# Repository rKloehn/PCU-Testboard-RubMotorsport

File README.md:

# PCU-Testboard-RubMotorsport

## Overview
The Powertrain Control Board test board (PCU test board for short) was developed in 2020 for the Drivetrain assembly in order to test the functions for the pneumatic switching and coupling of the RUB20 in advance. For this reason, the board contains all the necessary peripherals and connections required for the switching and coupling of the RUB20. The board is supplied with a 12V power supply (like the real PCU in the vehicle). On the board there are connections for two 24V solenoid valves and one proportional valve. Furthermore two sensors with 5V supply voltage each can be connected and the current value of the proportional valve can be read out. For testing the functionality of the switching and coupling process, three push buttons and an adjustment potentiometer are available. All mentioned components were fixed on the board. The control and regulation tasks are performed by a STM32F405RG. The microcontroller can be programmed via the SWD interface on the board. 

### Sensors
The drivetrain assembly has two sensors specified, which are required for a displacement control of the clutch. A Hall displacement transducer and a pressure sensor are used. The Hall displacement sensor is from the Novotechnik and is sponsored. The sensor is the TFD-4000 series (data sheet TDF-4000). The exact designation of the ordered sensor is: TFD-4021-624-211-401. This sensor has a measuring range of 24mm and a supply voltage of 5V (4.5...5V). The output signal is in the range of 0.25...4.75V and behaves ratiometrically to Ub. The characteristic curve is rising and the sensor is single-channel. Further characteristics can be taken from the data sheet. It is purchased from the company ADZ Nagano. The pressure sensor has a measurable pressure range of FILL IN DATA HERE and requires a supply voltage of 5V. The output signal, similar to the displacement sensor, is ratiometric and is in the range 0.5...4.5V. The sensor has three conductors and a rising characteristic. Further data can be taken from the data sheet (data sheet ADZ-SME).

### Actuators
The actuator system to be controlled by the test board consists of two 24V solenoid valves and one proportional valve. The 24V solenoid valves are from the company FESTO and have the following type description: VUVG-L10-P53E-T-M5_1P3. These are 5/3 [exhausted] valves with a switch-on time of 10ms, a switch-off time of 30ms and a switch-over time of 16ms. The coil is operated with 24V DC with 1W. Further values can be taken from the data sheet (data sheet solenoid valve). The proportional valve is also from the company FESTO and has the type description: VEAA-L-3-D11-Q4-A4-1-R1. The flow valve is controlled by setting the current from 4-20mA. The operating voltage is 24V DC and the electrical connection is a 4-pin M8 connector. Further data can be found in the data sheet.

### User interface
The aim of the test board is to check whether the intended path control and control of the circuit/clutch works. In order for this to happen early in the development process, the board must function completely independently of other boards (e.g. power supply board) or the steering wheel. Thus, it is necessary that the user has a possibility to simulate the actuation of the clutch or the start of a shifting process. For this reason, there are three push buttons on the board, two buttons for upshifting and downshifting and one button for venting the system at the push of a button. A rotary potentiometer also allows the on/off coupling of the motor gearbox. For programming, as mentioned above, the SWD interface is available to the user. The push buttons are all debounced with a corresponding circuit on the board. 

### Power supply
Several circuits are required for the power supply of the board. In total, exactly three voltage levels are available on the entire PCU test board. The input voltage of the board is 12V DC, which can be provided by a battery or power supply unit. The required current ranges from 0.1A to 0.3A, depending on which peripherals are used. The first voltage level of 5V is achieved by a UA78M05CDCY stepdown converter. The 5V voltage is then either used by the sensors or forms the input voltage for the 5V-3.3V voltage converter. Here a LM2937IMP is used. The 3.3V voltage circuit provides the supply voltage for the microcontroller. The 24V voltage circuit is realized by a StepUp circuit with the MC33063ADG. The 24V are used for the two valves.

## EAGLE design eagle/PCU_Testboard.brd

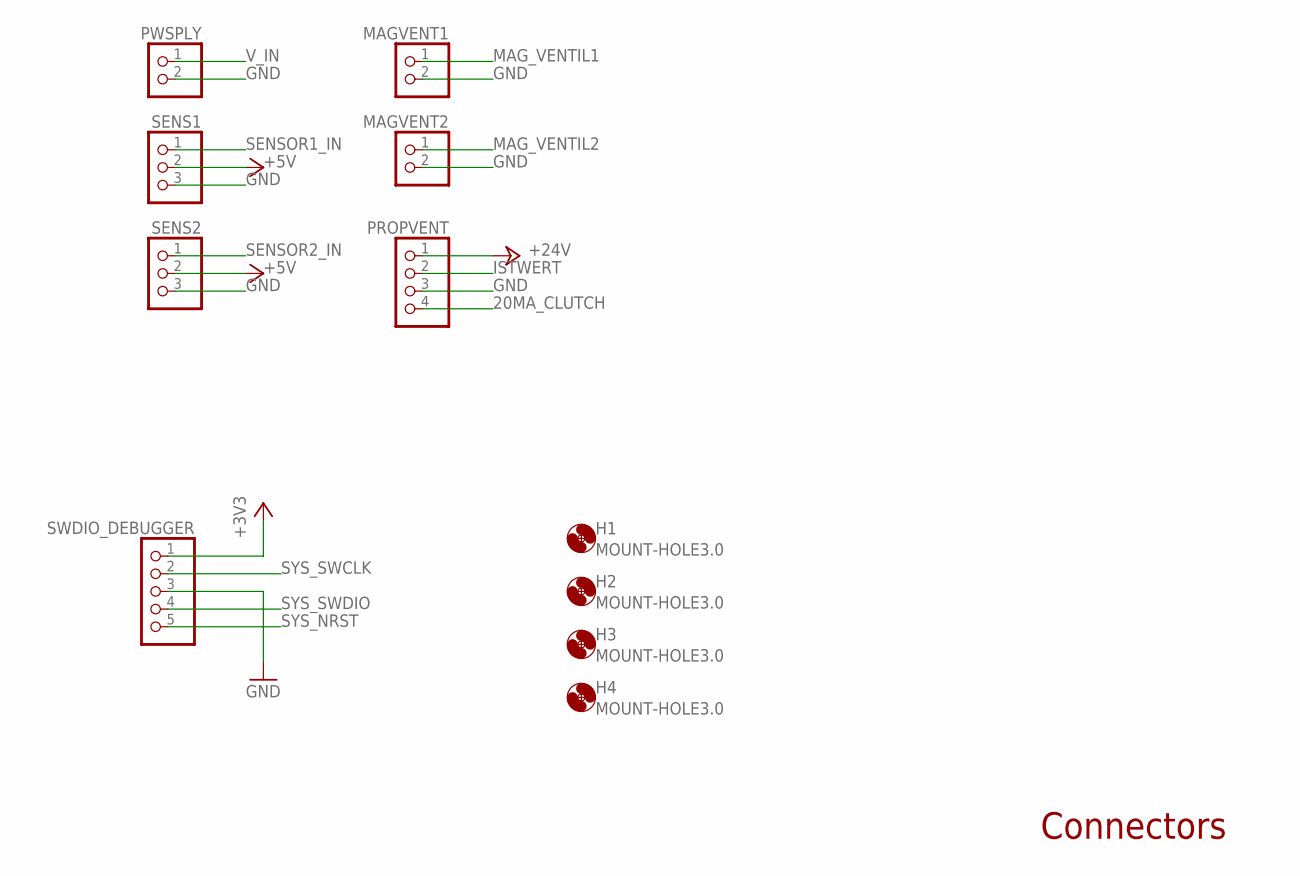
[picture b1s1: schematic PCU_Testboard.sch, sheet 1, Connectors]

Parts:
H1, H2, H3, H4: MOUNT-HOLE3.0; 3,0
MAGVENT1, MAGVENT2: PINHD-1X2; 1X02
PROPVENT: PINHD-1X4; 1X04
PWSPLY: PINHD-1X2; 1X02
SENS1, SENS2: PINHD-1X3; 1X03
SWDIO_DEBUGGER: PINHD-1X5; 1X05

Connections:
20MA_CLUTCH: PROPVENT.4; also elsewhere on the board
+3V3: SWDIO_DEBUGGER.1; also elsewhere on the board
+5V: SENS1.2, SENS2.2; also elsewhere on the board
+24V: PROPVENT.1; also elsewhere on the board
GND: MAGVENT1.2, MAGVENT2.2, PROPVENT.3, PWSPLY.2, SENS1.3, SENS2.3, SWDIO_DEBUGGER.3; also elsewhere on the board
ISTWERT: PROPVENT.2; also elsewhere on the board
MAG_VENTIL1: MAGVENT1.1; also elsewhere on the board
MAG_VENTIL2: MAGVENT2.1; also elsewhere on the board
SENSOR1_IN: SENS1.1; also elsewhere on the board
SENSOR2_IN: SENS2.1; also elsewhere on the board
SYS_NRST: SWDIO_DEBUGGER.5
SYS_SWCLK: SWDIO_DEBUGGER.2; also elsewhere on the board
SYS_SWDIO: SWDIO_DEBUGGER.4; also elsewhere on the board
V_IN: PWSPLY.1; also elsewhere on the board

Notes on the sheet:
Connectors

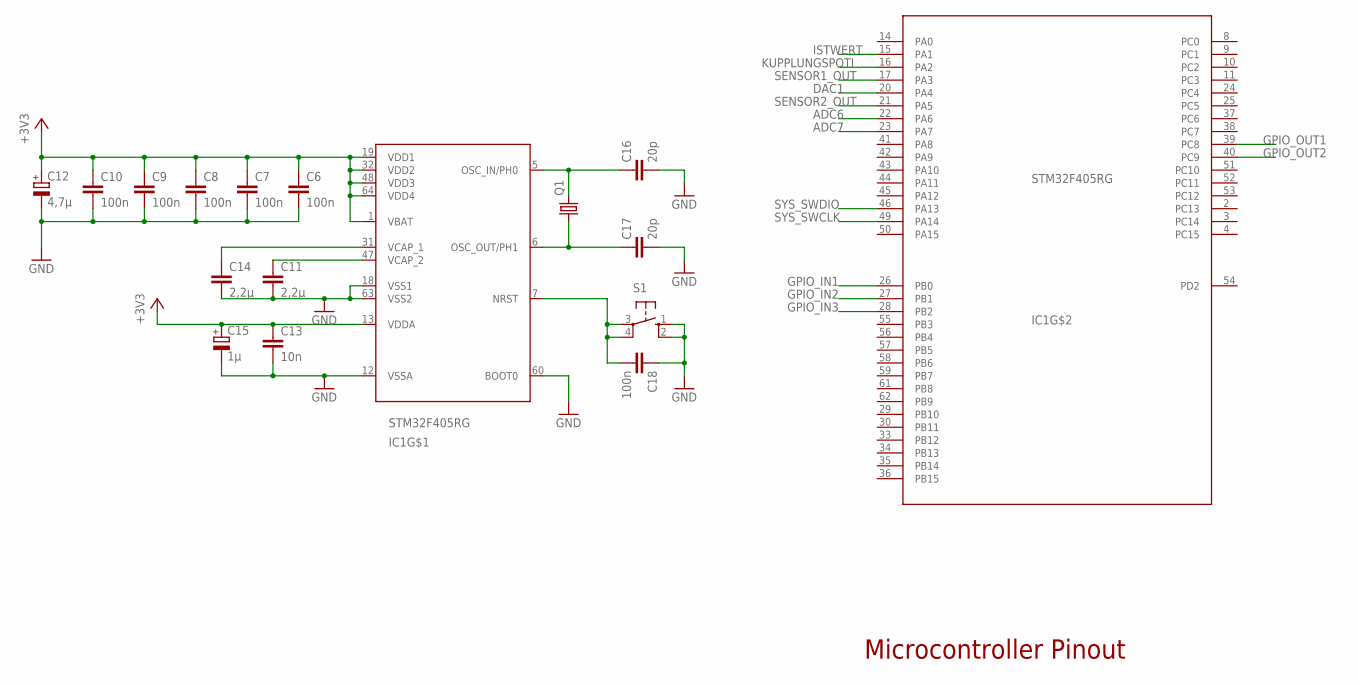
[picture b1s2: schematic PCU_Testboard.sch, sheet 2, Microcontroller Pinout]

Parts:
C6, C7, C8, C9, C10, C18: 100n; C0603
C11, C14: 2,2µ; C0603
C12: 4,7µ; 153CLV-0505
C13: 10n; C0603
C15: 1µ; 153CLV-0505
C16, C17: 20p; C0603
IC1: STM32F405RG; LQFP64
Q1: CRYSTALHC49UP; HC49UP
S1: 10-XX; B3F-10XX

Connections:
+3V3: C6.1, C7.1, C8.1, C9.1, C10.1, C12.+, C13.1, C15.+, IC1.1 (VBAT), IC1.13 (VDDA), IC1.19 (VDD1), IC1.32 (VDD2), IC1.48 (VDD3), IC1.64 (VDD4); also elsewhere on the board
ADC6: IC1.22 (PA6)
ADC7: IC1.23 (PA7)
DAC1: IC1.20 (PA4); also elsewhere on the board
GND: C6.2, C7.2, C8.2, C9.2, C10.2, C11.2, C12.-, C13.2, C14.2, C15.-, C16.2, C17.2, C18.1, IC1.12 (VSSA), IC1.18 (VSS1), IC1.60 (BOOT0), IC1.63 (VSS2), S1.1 (S), S1.2 (S1); also elsewhere on the board
GPIO_IN1: IC1.26 (PB0); also elsewhere on the board
GPIO_IN2: IC1.27 (PB1); also elsewhere on the board
GPIO_IN3: IC1.28 (PB2); also elsewhere on the board
GPIO_OUT1: IC1.39 (PC8); also elsewhere on the board
GPIO_OUT2: IC1.40 (PC9); also elsewhere on the board
ISTWERT: IC1.15 (PA1); also elsewhere on the board
KUPPLUNGSPOTI: IC1.16 (PA2); also elsewhere on the board
unnamed: C14.1, IC1.31 (VCAP_1)
unnamed: C11.1, IC1.47 (VCAP_2)
unnamed: C16.1, IC1.5 (OSC_IN/PH0), Q1.2
unnamed: C17.1, IC1.6 (OSC_OUT/PH1), Q1.1
unnamed: C18.2, IC1.7 (NRST), S1.3, S1.4 (P1)
SENSOR1_OUT: IC1.17 (PA3); also elsewhere on the board
SENSOR2_OUT: IC1.21 (PA5); also elsewhere on the board
SYS_SWCLK: IC1.49 (PA14); also elsewhere on the board
SYS_SWDIO: IC1.46 (PA13); also elsewhere on the board

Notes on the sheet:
Microcontroller Pinout

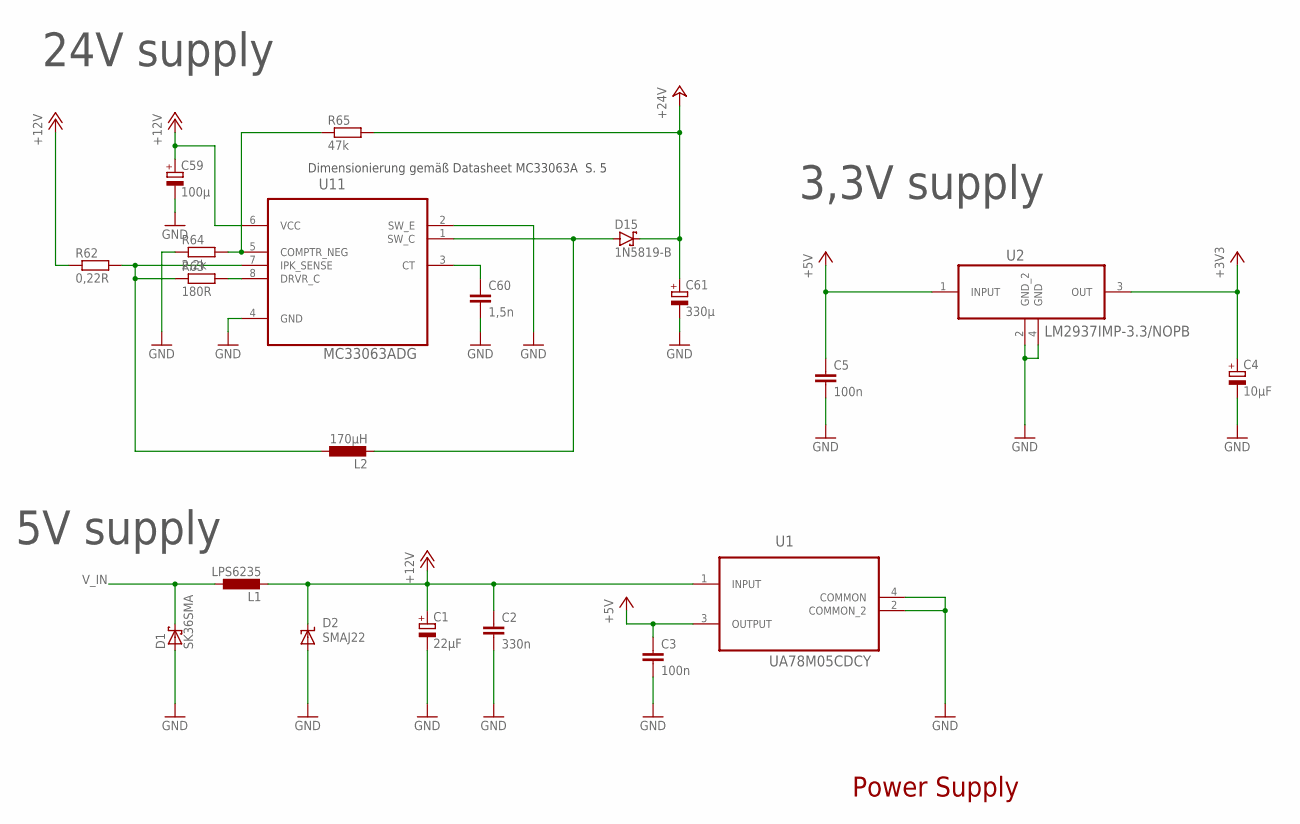
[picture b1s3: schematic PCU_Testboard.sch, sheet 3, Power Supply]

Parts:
C1: 22µF; 153CLV-0605
C2: 330n; C0603
C3, C5: 100n; C0603
C4: 10µF; 153CLV-0807
C59: 100µ; 150CLZ-0810
C60: 1,5n; C0603
C61: 330µ; 153CLV-1010
D1: SK36SMA; DO214AC
D2: SMAJ22; SMA-DO214AC
D15: 1N5819-B; DO41-7.6
L1: LPS6235
L2: 170µH; LPS6235
R62: 0,22R; R0603
R63: 180R; R0603
R64: 2,2k; R0603
R65: 47k; R0603
U1: UA78M05CDCY; SOT230P700X180-4N
U2: LM2937IMP-3.3/NOPB; SOT230P700X180-4N
U11: MC33063ADG; SOIC127P600X175-8N

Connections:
+3V3: C4.+, U2.3 (OUT); also elsewhere on the board
+5V: C3.1, C5.1, U1.3 (OUTPUT), U2.1 (INPUT); also elsewhere on the board
+12V: C1.+, C2.1, C59.+, D2.K (C), L1.2, R62.1, U1.1 (INPUT), U11.6 (VCC); also elsewhere on the board
+24V: C61.+, D15.C, R65.2; also elsewhere on the board
GND: C1.-, C2.2, C3.2, C4.-, C5.2, C59.-, C60.2, C61.-, D1.A, D2.A, R64.1, U1.2 (COMMON_2), U1.4 (COMMON), U2.2 (GND_2), U2.4 (GND), U11.2 (SW_E), U11.4 (GND); also elsewhere on the board
unnamed: C60.1, U11.3 (CT)
unnamed: L2.1, R62.2, R63.1, U11.7 (IPK_SENSE)
unnamed: R63.2, U11.8 (DRVR_C)
unnamed: D15.A, L2.2, U11.1 (SW_C)
unnamed: R64.2, R65.1, U11.5 (COMPTR_NEG)
V_IN: D1.C, L1.1; also elsewhere on the board

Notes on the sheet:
Dimensionierung gemäß Datasheet MC33063A S. 5
24V supply
3,3V supply
5V supply
Power Supply

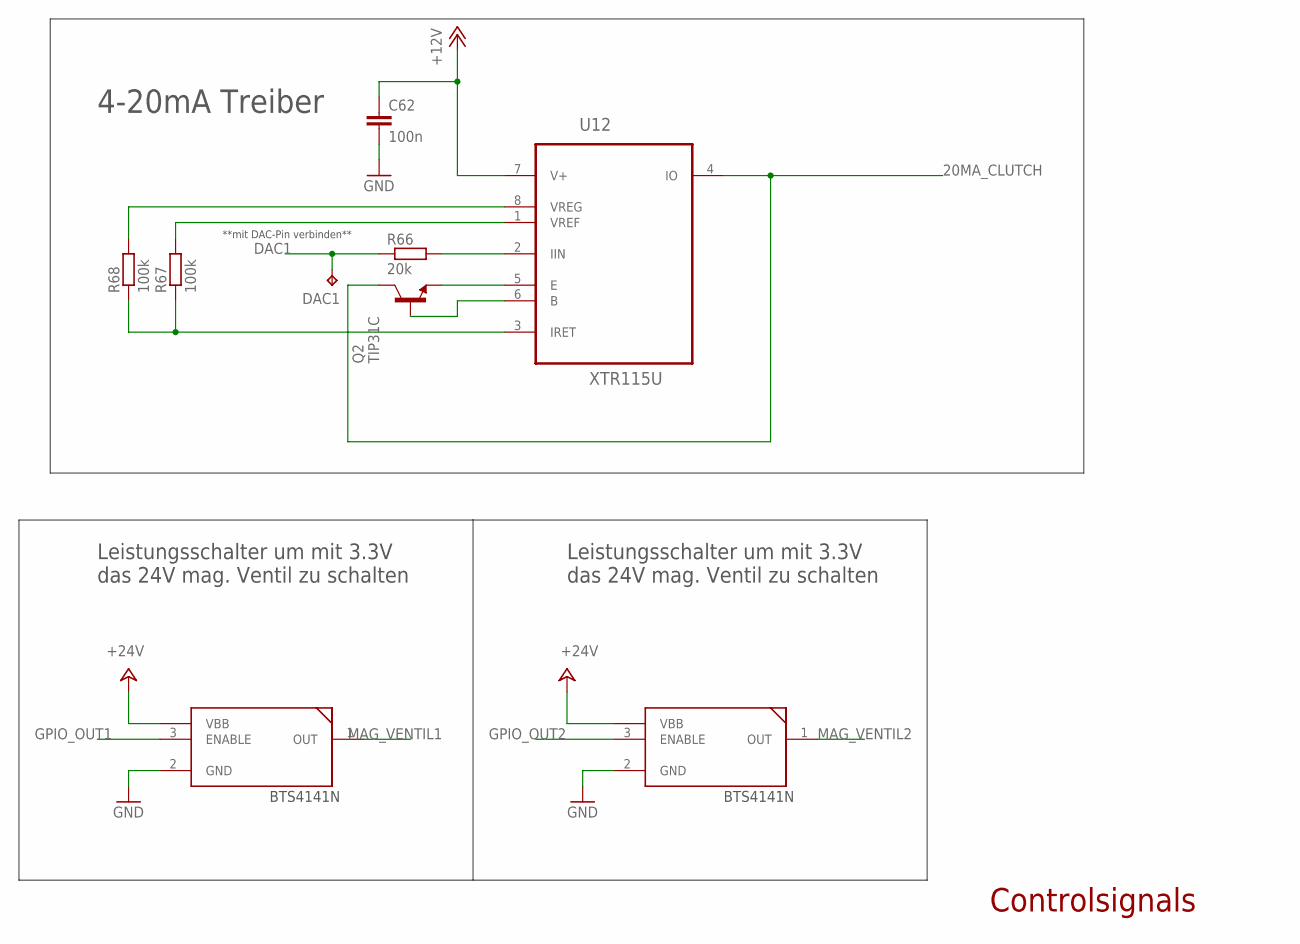
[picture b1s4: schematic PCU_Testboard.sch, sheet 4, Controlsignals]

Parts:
C62: 100n; C0603
DAC1: TPB1,27; B1,27
Q2: TIP31C; TO220
R66: 20k; R0603
R67, R68: 100k; R0603
U12: XTR115U; SOIC127P600X175-8N
U$1, U$4: BTS4141N; SOT223

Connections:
20MA_CLUTCH: Q2.2 (C), U12.4 (IO); also elsewhere on the board
+12V: C62.1, U12.7 (V+); also elsewhere on the board
+24V: U$1.4 (VBB), U$4.4 (VBB); also elsewhere on the board
DAC1: DAC1.TP, R66.1; also elsewhere on the board
GND: C62.2, U$1.2 (GND), U$4.2 (GND); also elsewhere on the board
GPIO_OUT1: U$1.3 (ENABLE); also elsewhere on the board
GPIO_OUT2: U$4.3 (ENABLE); also elsewhere on the board
MAG_VENTIL1: U$1.1 (OUT); also elsewhere on the board
MAG_VENTIL2: U$4.1 (OUT); also elsewhere on the board
unnamed: R66.2, U12.2 (IIN)
unnamed: Q2.3 (E), U12.5 (E)
unnamed: Q2.1 (B), U12.6 (B)
unnamed: R67.2, U12.1 (VREF)
unnamed: R68.2, U12.8 (VREG)
unnamed: R67.1, R68.1, U12.3 (IRET)

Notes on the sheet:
**mit DAC-Pin verbinden**
4-20mA Treiber
Controlsignals
Leistungsschalter um mit 3.3V das 24V mag. Ventil zu schalten

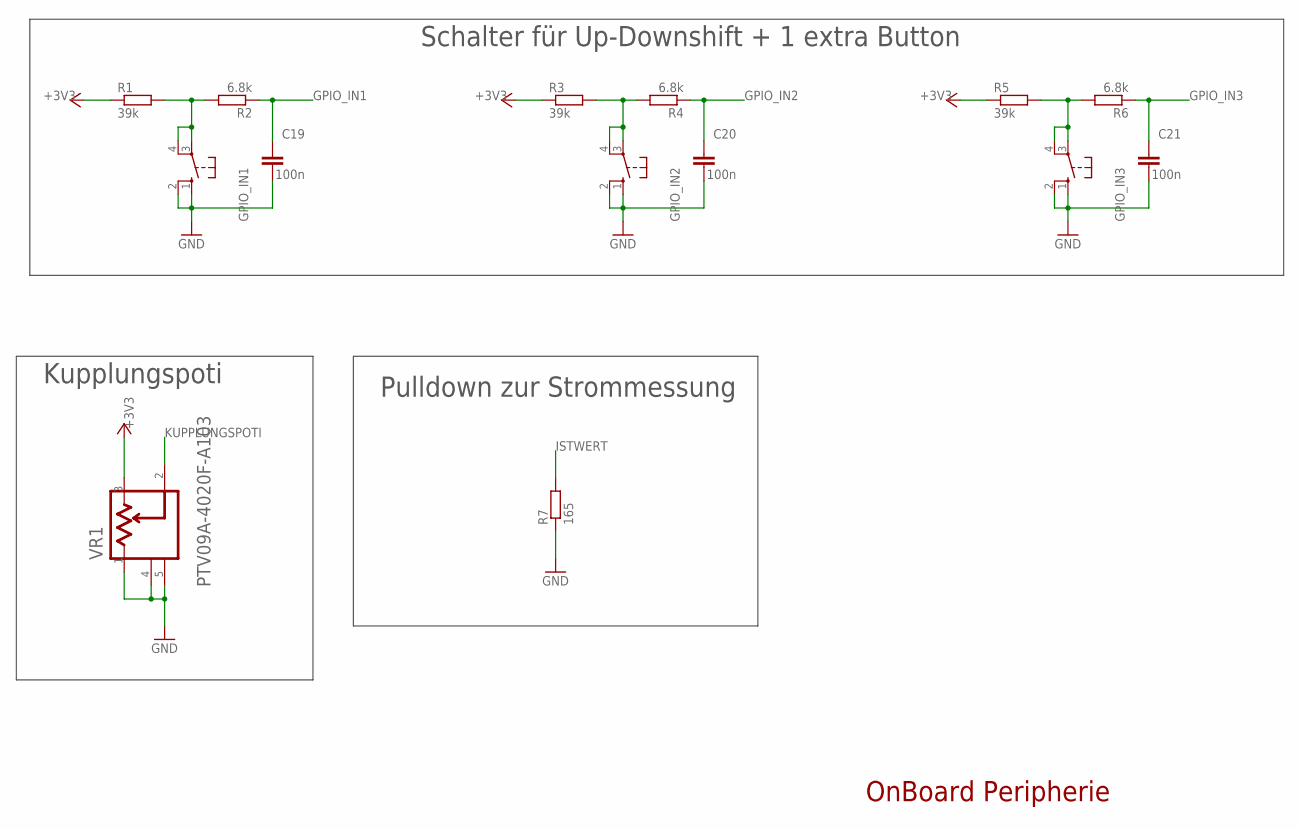
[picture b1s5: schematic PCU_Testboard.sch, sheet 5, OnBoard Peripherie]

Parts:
C19, C20, C21: 100n; C0603
GPIO_IN1, GPIO_IN2, GPIO_IN3: 10-XX; B3F-10XX
R1, R3, R5: 39k; R0805
R2, R4, R6: 6.8k; R0805
R7: 165; R0805
VR1: BOURNS_PTV09A-4020F-A103BOURNS_PTV09A-4020F-A103_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; BOURNS_PTV09A-4020F-A103_0

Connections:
+3V3: R1.1, R3.1, R5.1, VR1.3; also elsewhere on the board
GND: C19.2, C20.2, C21.2, GPIO_IN1.1 (S), GPIO_IN1.2 (S1), GPIO_IN2.1 (S), GPIO_IN2.2 (S1), GPIO_IN3.1 (S), GPIO_IN3.2 (S1), R7.1, VR1.1, VR1.4 (MNT_1), VR1.5 (MNT_2); also elsewhere on the board
GPIO_IN1: C19.1, R2.1; also elsewhere on the board
GPIO_IN2: C20.1, R4.1; also elsewhere on the board
GPIO_IN3: C21.1, R6.1; also elsewhere on the board
ISTWERT: R7.2; also elsewhere on the board
KUPPLUNGSPOTI: VR1.2; also elsewhere on the board
unnamed: GPIO_IN1.3, GPIO_IN1.4 (P1), R1.2, R2.2
unnamed: GPIO_IN2.3, GPIO_IN2.4 (P1), R3.2, R4.2
unnamed: GPIO_IN3.3, GPIO_IN3.4 (P1), R5.2, R6.2

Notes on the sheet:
OnBoard Peripherie
Schalter für Up-Downshift + 1 extra Button
Pulldown zur Strommessung
Kupplungspoti

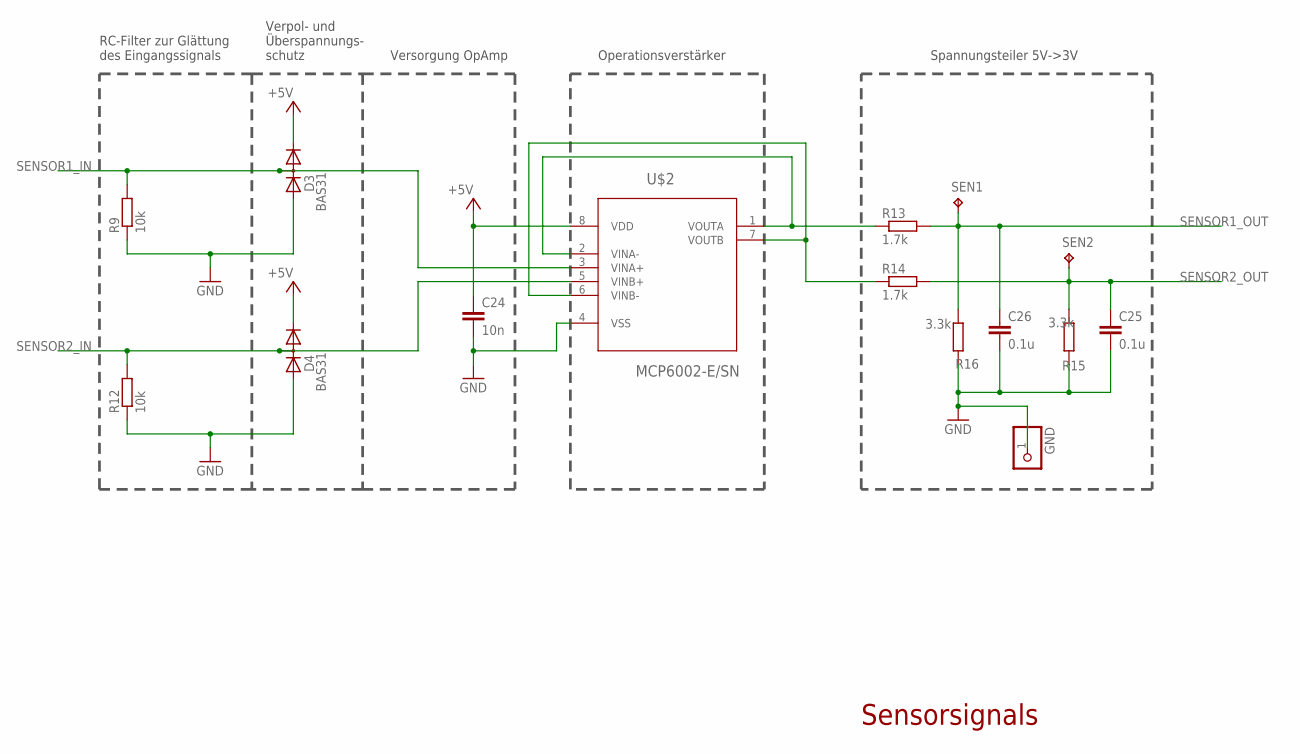
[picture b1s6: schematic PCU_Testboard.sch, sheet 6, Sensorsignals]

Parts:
C24: 10n; C0603
C25, C26: 0.1u; C0603
D3, D4: BAS31; SOT23
GND: PINHD-1X1; 1X01
R9, R12: 10k; R0805
R13, R14: 1.7k; R0805
R15, R16: 3.3k; R0805
SEN1, SEN2: TPB1,27; B1,27
U$2: MCP6002-E/SN; SOIC127P600X175-8N

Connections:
+5V: C24.1, D3.2 (C), D4.2 (C), U$2.8 (VDD); also elsewhere on the board
GND: C24.2, C25.2, C26.2, D3.1 (A), D4.1 (A), GND.1, R9.1, R12.1, R15.2, R16.1, U$2.4 (VSS); also elsewhere on the board
unnamed: R13.1, U$2.1 (VOUTA), U$2.2 (VINA-)
unnamed: R14.1, U$2.6 (VINB-), U$2.7 (VOUTB)
SENSOR1_IN: D3.3 (AC), R9.2, U$2.3 (VINA+); also elsewhere on the board
SENSOR1_OUT: C26.1, R13.2, R16.2, SEN1.TP; also elsewhere on the board
SENSOR2_IN: D4.3 (AC), R12.2, U$2.5 (VINB+); also elsewhere on the board
SENSOR2_OUT: C25.1, R14.2, R15.1, SEN2.TP; also elsewhere on the board

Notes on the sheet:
RC-Filter zur Glättung des Eingangssignals
Verpol- und Überspannungs- schutz
Versorgung OpAmp
Spannungsteiler 5V->3V
Operationsverstärker
Sensorsignals

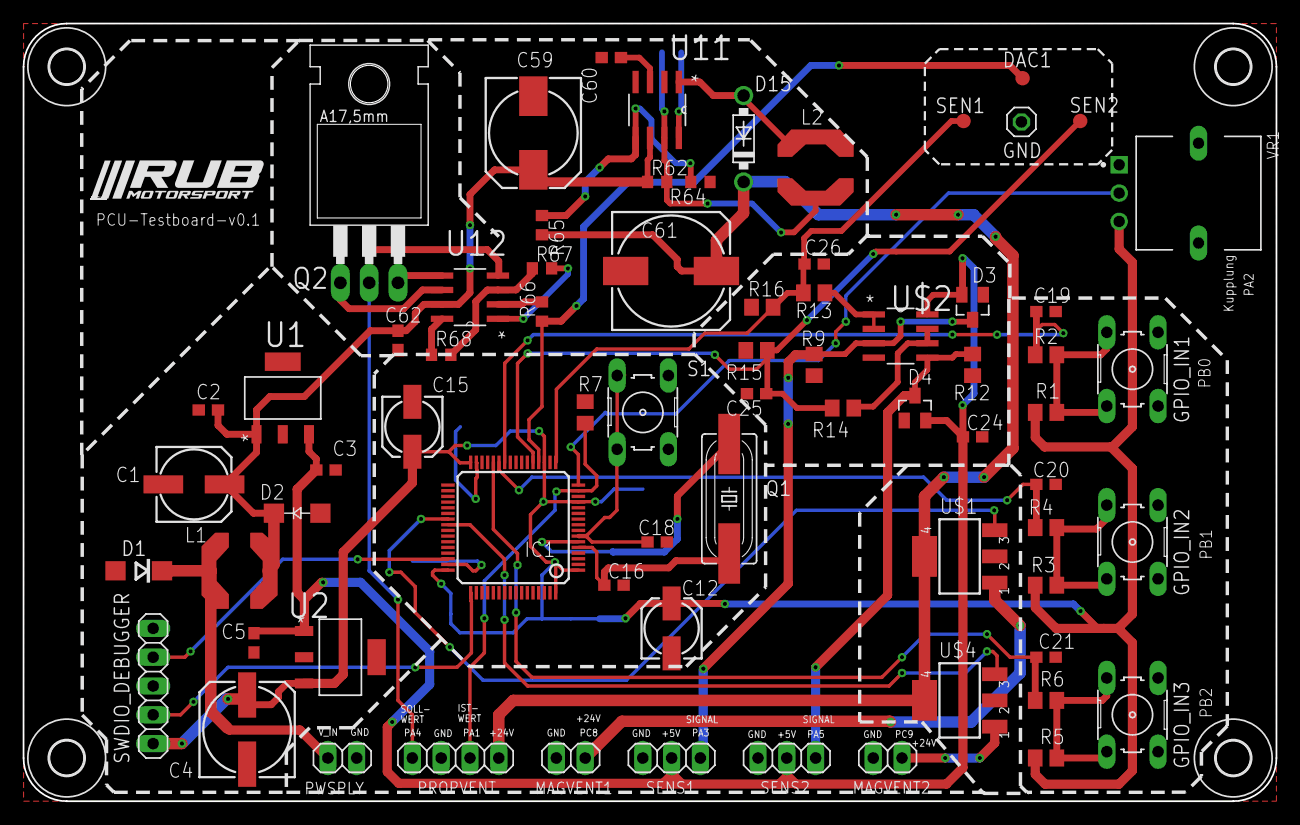
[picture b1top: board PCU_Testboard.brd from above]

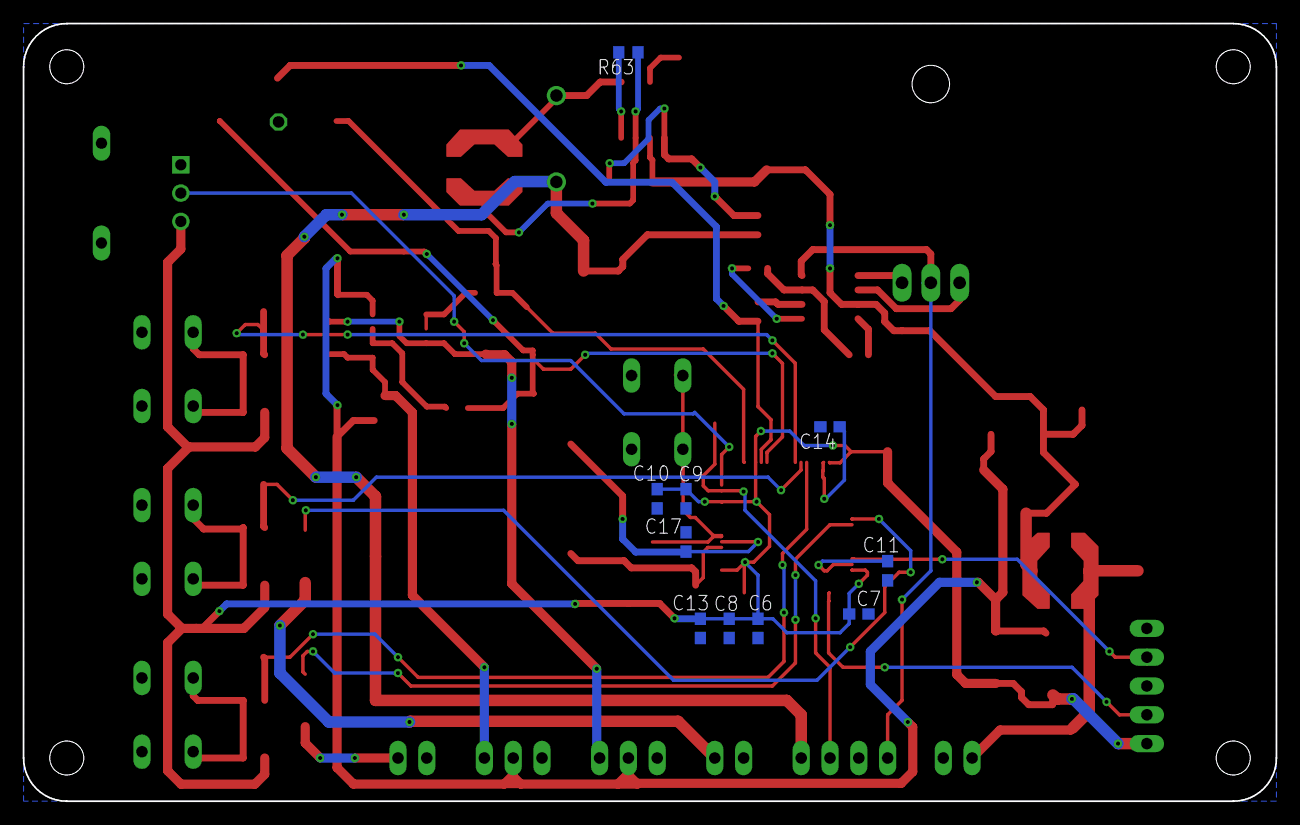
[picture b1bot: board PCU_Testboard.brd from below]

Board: 2 copper layers, 110.5 x 68.6 mm, 85 parts (10 on the bottom side), 44 nets.
